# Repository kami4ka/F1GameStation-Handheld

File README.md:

<p align="right"><b>English</b> · <a href="README.uk.md">Українська</a></p>

<h1 align="center">F1GameStation</h1>

<p align="center">
  An open-source, PSP-style handheld for 8- and 16-bit games,<br>
  built around the Allwinner F1C200s and running a port of MiyooCFW.<br>
  <b>About $25 in parts, and every file is open.</b>
</p>

<p align="center">

</p>

<p align="center">
  <a href="https://kami4ka.github.io/F1GameStation-Handheld/"><b>Interactive 3D model and board viewer</b></a> ·
  <a href="docs/BUILD.md"><b>Build guide</b></a> ·
  <a href="https://kami4ka.github.io/F1GameStation-Handheld/ibom.html"><b>Interactive BOM</b></a> ·
  <a href="firmware/README.md"><b>Firmware</b></a>
</p>

> [!NOTE]
> **Rev 1 is a fully working console**: LCD, sound, buttons, battery, backlight and USB all work, and it
> plays games. It is still a first revision with [known issues](#known-issues), so expect some hand work
> while building one.

<p align="center">
  
</p>

## What it is

| | |
| --- | --- |
| **SoC** | Allwinner F1C200s (ARM926EJ-S, 64 MB DDR in package) |
| **Display** | 4.3" 480×272 RGB panel, 40-pin FPC (FPC043CS4001) |
| **Controls** | D-pad, A/B/X/Y, START, SELECT, MENU, PSP-style L/R triggers, side power button |
| **Power** | 1S Li-ion 606090 cell, IP5306 charger and boost, USB-C |
| **Audio** | SoC codec, NS4150B amplifier, on-board speaker |
| **Storage** | microSD (boot and games), optional 16 MB SPI flash |
| **Board** | 176 × 70 mm, 4 layers (JLC04161H-7628), JLCPCB assembly |
| **Case** | 186 × 80 mm, FDM-printed in PETG, M2 heat-set inserts |
| **Cost** | about $25 per unit (board share, parts, LCD, battery, filament) |
| **Firmware** | MiyooCFW 2.0 with a 480×272 kernel driver, a 480×272 gmenu2x and a cover-flow launcher |

## Repository

```
hardware/       KiCad 10 project, fab package (Gerbers, BOM with LCSC numbers,
                positions, schematic PDF, interactive BOM), PCBA STEP
enclosure/      print/   STL and 3MF files, two-colour labelled caps for Bambu printers
                source/  Fusion 360 archives (.f3d), STEP, parametric Fusion scripts
firmware/       miyoocfw/  kernel patches, device tree, SD card scripts, Docker build
                launcher/  the cover-flow game launcher
                emulator/  a QEMU model of the handheld for development without hardware
docs/           build guide, images
site/           the project site (3D viewer, KiCanvas), deployed to GitHub Pages
```

## Build one

The [build guide](docs/BUILD.md) walks through it step by step:

1. **Order the board** from JLCPCB with the files in [`hardware/production`](hardware/production).
2. **Finish the assembly**: the SoC and DC-DC are supplied by you, then the LCD, battery and speaker.
3. **Build the firmware** from source and flash it to a microSD card ([firmware/README.md](firmware/README.md)).
4. **Print the case** from [`enclosure/print`](enclosure/print).
5. **Close it up** with four M2 heat-set inserts, two filament pins and four M2 × 12 screws.

No hardware yet? The [emulator](firmware/emulator/README.md) boots the same SD card image on a Mac.

## Status

| Block | State |
| --- | --- |
| SoC, DRAM, FEL, U-Boot, SD boot | ✅ working on two boards |
| Power rails (EA3059C bucks, 3V0 LDO) | ✅ working |
| Buttons (13 inputs) | ✅ working, see PA1–PA3 below |
| MiyooCFW kernel, menu, emulators | ✅ boots and runs |
| LCD | ✅ working |
| Audio (codec, amplifier, speaker) | ✅ working |
| Battery gauge | ✅ working |
| Backlight | ✅ working |
| USB high speed | ✅ working |

### Known issues

- **L, R and MENU (PA1, PA2, PA3) have no pull-ups.** These pins belong to the SoC's touch-panel block,
  and their internal pull-ups have no effect. The firmware works around it by charging each line and
  reading it straight away. Rev 2 should add 10 kΩ external pull-ups to 3V3.
- **No pin-1 marks on the silkscreen.** Check the orientation of every IC, LED and polarised part
  against the [interactive BOM](hardware/production/F1GameStation-ibom.html) before soldering.
- The L/R trigger switches have no locating holes for their pegs; trim the pegs and fit them by hand.

## Gallery

Launcher screenshots are emulator captures with homebrew games and placeholder art.

## Credits

- [MiyooCFW](https://github.com/MiyooCFW) for the kernel, root filesystem, gmenu2x and the emulator builds this firmware is based on.
- The F1C200s core (SoC, DRAM, power, SD) comes from [FPVault](https://github.com/kami4ka/FPVault), the author's open-source onboard DVR for analog FPV, where it was tested over three board revisions.
- [KiCanvas](https://kicanvas.org), [InteractiveHtmlBom](https://github.com/openscopeproject/InteractiveHtmlBom) and [three.js](https://threejs.org) for the project site.

## License

- Hardware (`hardware/`, `enclosure/`): [CERN-OHL-S-2.0](hardware/LICENSE)
- Firmware (`firmware/`, `site/tools/`): [GPL-2.0](firmware/LICENSE). Third-party parts keep their own licences (DejaVu fonts, MiyooCFW, QEMU).
- Documentation and images (`docs/`): [CC BY-SA 4.0](docs/LICENSE)

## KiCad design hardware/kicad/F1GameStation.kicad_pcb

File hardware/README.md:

# Hardware

KiCad 10 project for the F1GameStation main board, Rev 1.

| Path | What |
| --- | --- |
| `kicad/F1GameStation.kicad_pro` | project; open this in KiCad |
| `kicad/*.kicad_sch` | schematic: top sheet plus `soc`, `power`, `storage`, `display`, `audio`, `buttons` |
| `kicad/F1GameStation.kicad_pcb` | 4-layer board, 176 × 70 mm |
| `kicad/libraries/` | project symbols, footprints and 3D models (most come from the LCSC/EasyEDA library) |
| `production/F1GameStation.zip` | Gerbers and drill files for JLCPCB |
| `production/bom.csv` | BOM grouped by part, with LCSC numbers |
| `production/positions.csv` | pick-and-place (both sides) |
| `production/netlist.ipc` | IPC-D-356 netlist for the electrical test |
| `production/F1GameStation-schematic.pdf` | schematic as PDF |
| `production/F1GameStation-ibom.html` | interactive BOM, open in a browser |
| `3d/F1GameStation_PCBA.step` | assembled board for mechanical CAD |

The board can also be browsed without KiCad on the
[project site](https://kami4ka.github.io/F1GameStation-Handheld/#hardware).

## Design notes

- **Stackup:** L1 signal, L2 GND, L3 power planes (3V3, 2V5, 1V2), L4 signal. Ground is
  carried by the L2 plane, outer pours and stitching vias, not by traces.
- **Sides:** buttons, LEDs and the speaker are on the front; every other part is on the back.
  Parts under the battery stay below 2.4 mm.
- **USB:** the D+/D− pair is coupled 0.16/0.1 mm with a 0.2 mm pour gap, about 90 Ω on JLC04161H-7628.
- **No vias in SMD pads**, except the thermal vias under exposed pads.
- **Power:** IP5306 charges the 1S cell from USB-C and boosts it to 5 V. An EA3059C makes 3V3, 2V5 and
  1V2; an XC6206 makes 3V0. The backlight driver is an MP3202 (PT4103 footprint and pinout).
- **Battery gauge:** +BATT through a 200k/100k divider to LRADC0 (KEYADC, SoC pin 79).
- **LCD:** 40-pin RGB565 panel on J2 (AFC24-S40FIA-00, contacts on both sides). Its pin numbering is
  reversed in the footprint because the panel's pin 1 lands on connector contact 40.
- **Debug:** UART0 on the TX/RX/GND pads on the back (2.54 mm row), FEL button SW2, Reset SW1.

## Rev 1 issues

- PA1–PA3 (MENU, L, R) need external pull-ups; firmware works around it for now.
- No pin-1 markers on the silkscreen.
- No locating holes for the L/R trigger switch pegs.

## License

[CERN-OHL-S-2.0](LICENSE).

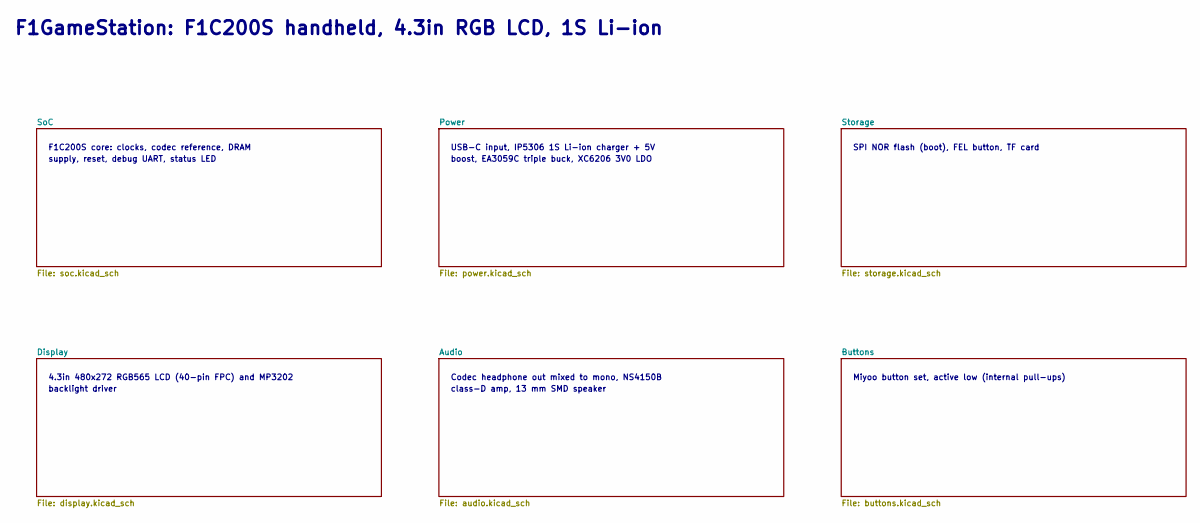
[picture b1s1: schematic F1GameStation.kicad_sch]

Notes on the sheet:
F1GameStation: F1C200S handheld, 4.3in RGB LCD, 1S Li-ion
F1C200S core: clocks, codec reference, DRAM
supply, reset, debug UART, status LED
USB-C input, IP5306 1S Li-ion charger + 5V
boost, EA3059C triple buck, XC6206 3V0 LDO
SPI NOR flash (boot), FEL button, TF card
4.3in 480x272 RGB565 LCD (40-pin FPC) and MP3202
backlight driver
Codec headphone out mixed to mono, NS4150B
class-D amp, 13 mm SMD speaker
Miyoo button set, active low (internal pull-ups)

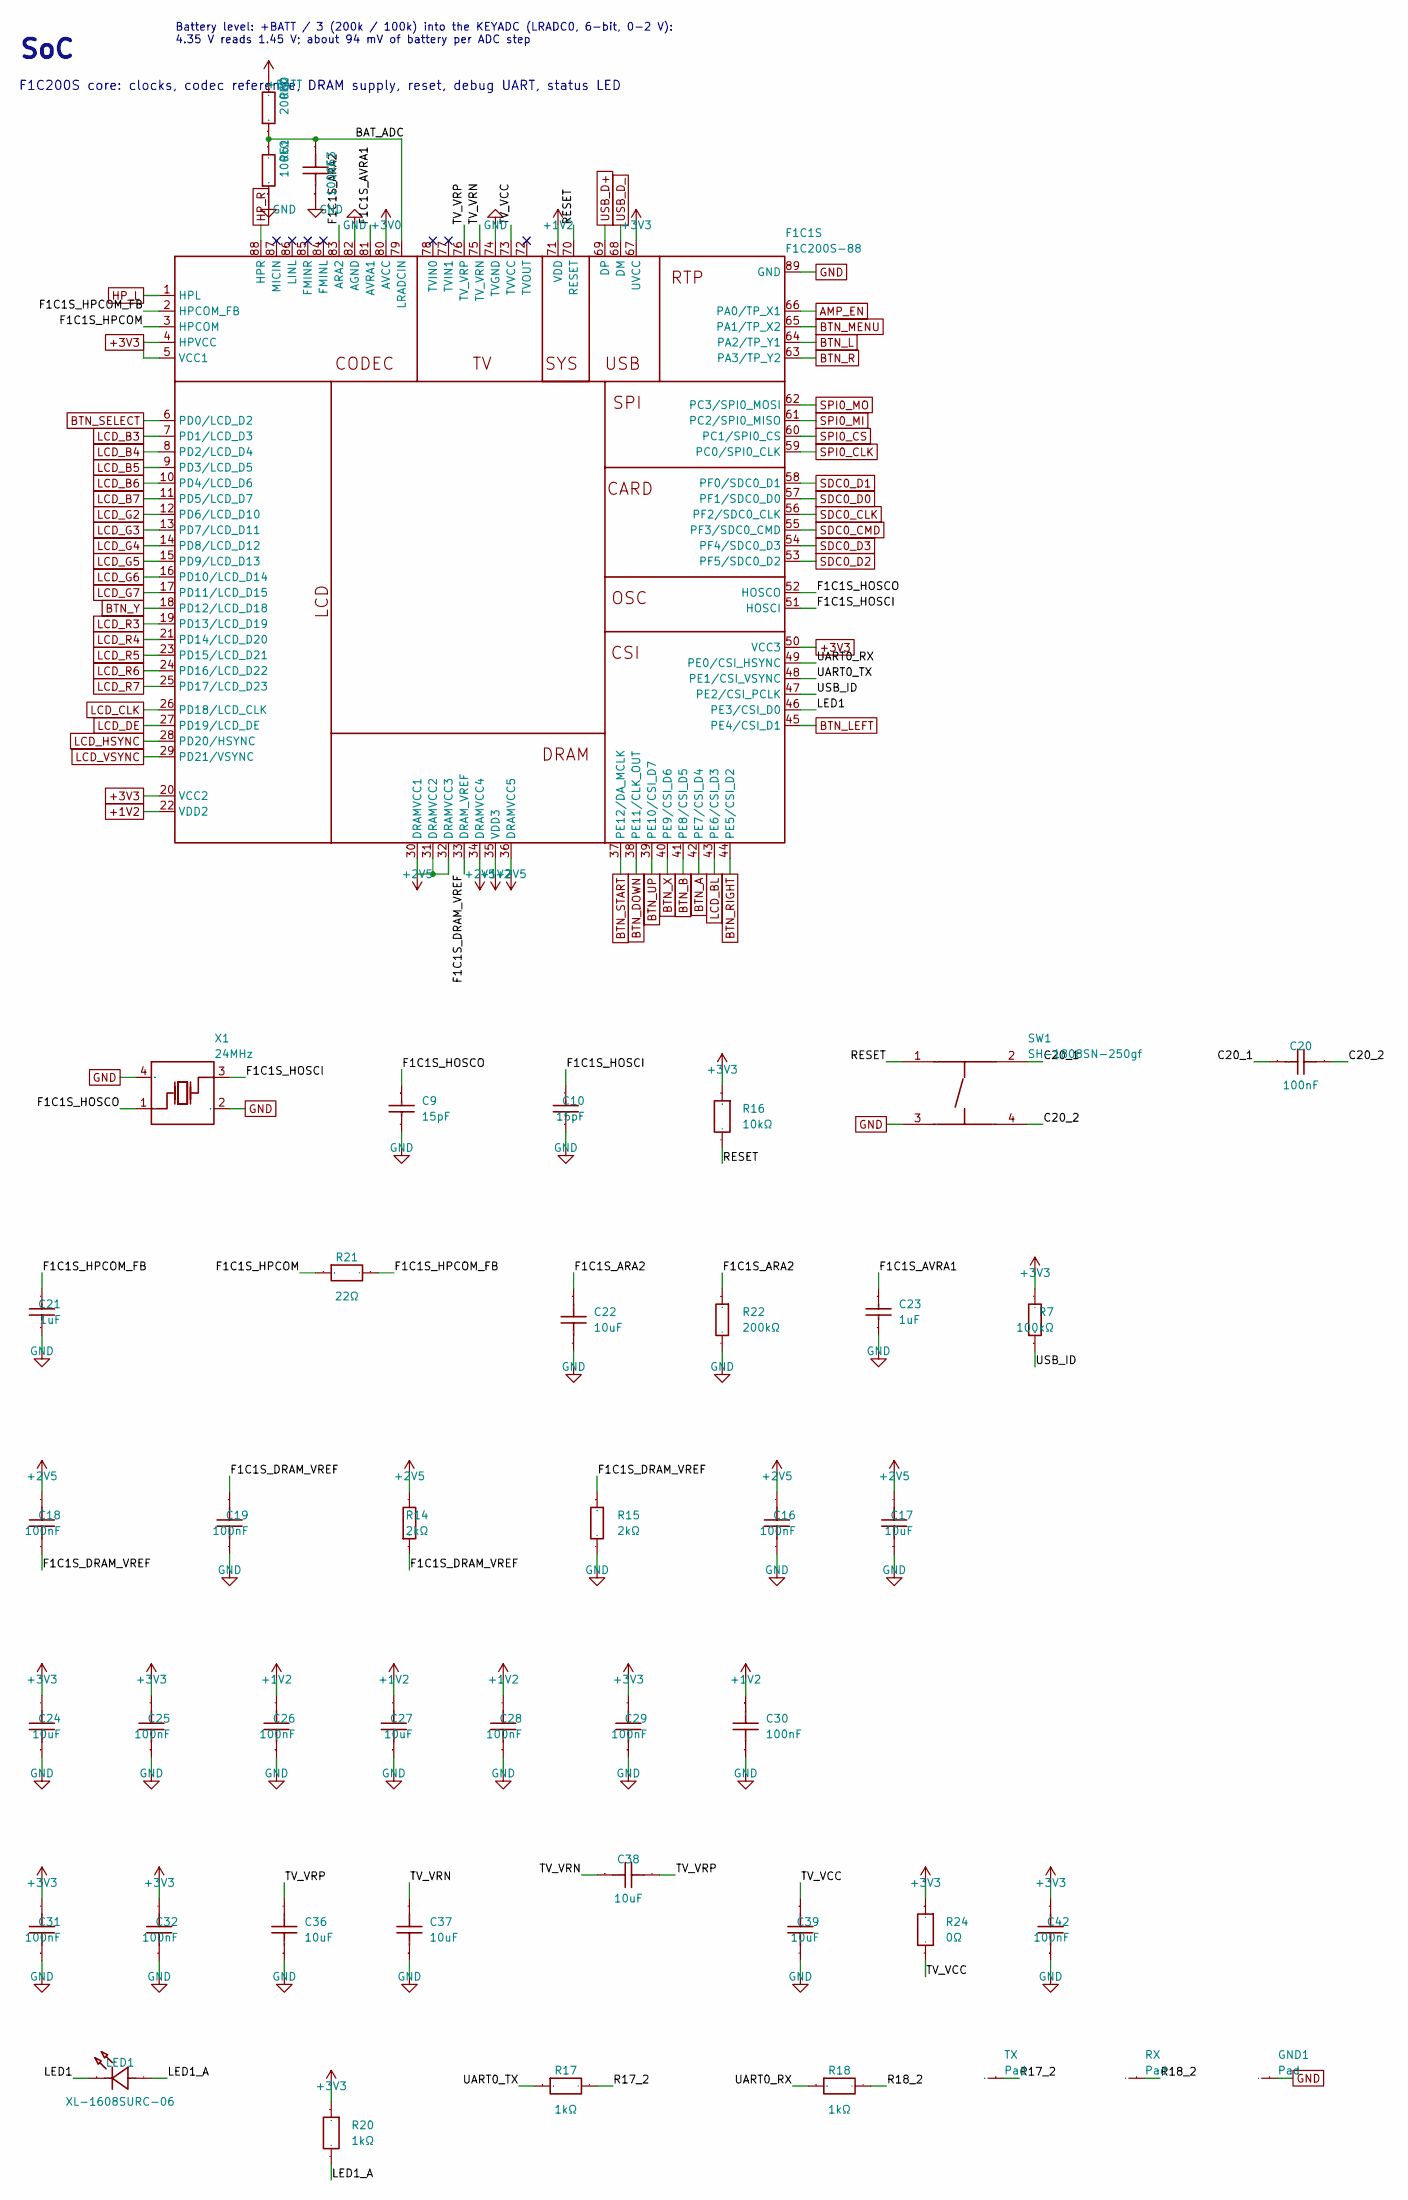
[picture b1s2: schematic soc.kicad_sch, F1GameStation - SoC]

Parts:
C9, C10: 15pF; C0603; Tolerance ±5%; Voltage Rating 50V; Manufacturer Part CL10C150JB8NNNC; LCSC C1644
C16, C18, C19, C20, C25, C26, C28, C29, C30, C31, C32, C63: 100nF; C0603; Tolerance ±10%; Voltage Rating 50V; Manufacturer Part CL10B104KB8NNNC; LCSC C1591
C17, C22, C24, C27: 10uF; C0603; Tolerance ±20%; Voltage Rating 25V; Manufacturer Part TCC0603X5R106M160CT; LCSC C380317
C21, C23: 1uF; C0603; Tolerance ±10%; Voltage Rating 25V; Manufacturer Part CL10B105KA8NNNC; LCSC C29936
C36, C37, C38, C39: 10uF; C0603; Tolerance ±20%; Voltage Rating 16V; Manufacturer Part TCC0603X5R106M160CT; LCSC C380317
C42: 100nF; C0603; Tolerance ±10%; Voltage Rated 50V; Manufacturer Part CC0603KRX7R9BB104; LCSC C14663
F1C1S: F1C200S-88; QFN-88_L10.0-W10.0-P0.40-BL-EP; Manufacturer Part F1C200S; LCSC C2879851
GND1: Pad; PAD
LED1: XL-1608SURC-06; LED0603-RD_RED; Voltage - Forward(Vf) 2.3V; Manufacturer Part XL-1608SURC-06; LCSC C965799
R7, R51: 100kΩ; R0603; Tolerance ±1%; Voltage-Supply(Max) 75V; Manufacturer Part RC0603FR-07100KL; LCSC C14675
R14, R15: 2kΩ; R0603; Tolerance ±1%; Voltage-Supply(Max) 75V; Manufacturer Part RC0603FR-072KL; LCSC C105576
R16: 10kΩ; R0603; Tolerance ±1%; Manufacturer Part CRCW060310K0FKEA; LCSC C844918
R17, R18, R20: 1kΩ; R0603; Tolerance ±1%; Voltage-Supply(Max) 75V; Manufacturer Part FRC0603F1001TS; LCSC C2907002
R21: 22Ω; R0603; Tolerance ±1%; Voltage-Supply(Max) 75V; Manufacturer Part FRC0603F22R0TS; LCSC C2930077
R22, R50: 200kΩ; R0603; Tolerance ±1%; Manufacturer Part RC0603FR-07200KL; LCSC C105574
R24: 0Ω; R0603; Tolerance ±5%; Voltage-Supply(Max) 75V; Manufacturer Part 1RC0603J0000; LCSC C54531634
RX: Pad; PAD
SW1: SH-1808SN-250gf; SW-SMD_4P-L4.2-W3.4-P2.15-LS5.2; Voltage Rating 12V; Manufacturer Part SH-1808SN-250gf; LCSC C52092028
TX: Pad; PAD
X1: 24MHz; CRYSTAL-SMD_4P-L3.2-W2.5-BL; Manufacturer Part X322524MOB4SI; LCSC C70590

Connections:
+1V2: C26.2, C27.2, C28.2, C30.1, F1C1S.22 (VDD2), F1C1S.35 (VDD3), F1C1S.71 (VDD); also elsewhere on the board
+2V5: C16.2, C17.2, C18.2, F1C1S.30 (DRAMVCC1), F1C1S.31 (DRAMVCC2), F1C1S.32 (DRAMVCC3), F1C1S.34 (DRAMVCC4), F1C1S.36 (DRAMVCC5), R14.2; also elsewhere on the board
+3V0: F1C1S.80 (AVCC); also elsewhere on the board
+3V3: C24.2, C25.2, C29.2, C31.2, C32.2, C42.2, F1C1S.4 (HPVCC), F1C1S.5 (VCC1), F1C1S.20 (VCC2), F1C1S.50 (VCC3), F1C1S.67 (UVCC), R7.2, R16.1, R20.1, R24.1; also elsewhere on the board
+BATT: R50.2; also elsewhere on the board
/SoC/BAT_ADC: C63.2, F1C1S.79 (LRADCIN), R50.1, R51.2
/SoC/C20_1: C20.1, SW1.2
/SoC/C20_2: C20.2, SW1.4
/SoC/F1C1S_ARA2: C22.1, F1C1S.83 (ARA2), R22.1
/SoC/F1C1S_AVRA1: C23.1, F1C1S.81 (AVRA1)
/SoC/F1C1S_DRAM_VREF: C18.1, C19.2, F1C1S.33 (DRAM_VREF), R14.1, R15.1
/SoC/F1C1S_HOSCI: C10.2, F1C1S.51 (HOSCI), X1.3 (OSC2)
/SoC/F1C1S_HOSCO: C9.1, F1C1S.52 (HOSCO), X1.1 (OSC1)
/SoC/F1C1S_HPCOM: F1C1S.3 (HPCOM), R21.1
/SoC/F1C1S_HPCOM_FB: C21.2, F1C1S.2 (HPCOM_FB), R21.2
/SoC/LED1: F1C1S.46 (PE3/CSI_D0), LED1.1 (K)
/SoC/LED1_A: LED1.2 (A), R20.2
/SoC/R17_2: R17.2, TX.1
/SoC/R18_2: R18.2, RX.1
/SoC/RESET: F1C1S.70 (RESET), R16.2, SW1.1
/SoC/TV_VCC: C39.1, F1C1S.73 (TVVCC), R24.2
/SoC/TV_VRN: C37.2, C38.1, F1C1S.75 (TV_VRN)
/SoC/TV_VRP: C36.2, C38.2, F1C1S.76 (TV_VRP)
/SoC/UART0_RX: F1C1S.49 (PE0/CSI_HSYNC), R18.1
/SoC/UART0_TX: F1C1S.48 (PE1/CSI_VSYNC), R17.1
/SoC/USB_ID: F1C1S.47 (PE2/CSI_PCLK), R7.1
AMP_EN: F1C1S.66 (PA0/TP_X1); also elsewhere on the board
BTN_A: F1C1S.42 (PE7/CSI_D4); also elsewhere on the board
BTN_B: F1C1S.41 (PE8/CSI_D5); also elsewhere on the board
BTN_DOWN: F1C1S.38 (PE11/CLK_OUT); also elsewhere on the board
BTN_L: F1C1S.64 (PA2/TP_Y1); also elsewhere on the board
BTN_LEFT: F1C1S.45 (PE4/CSI_D1); also elsewhere on the board
BTN_MENU: F1C1S.65 (PA1/TP_X2); also elsewhere on the board
BTN_R: F1C1S.63 (PA3/TP_Y2); also elsewhere on the board
BTN_RIGHT: F1C1S.44 (PE5/CSI_D2); also elsewhere on the board
BTN_SELECT: F1C1S.6 (PD0/LCD_D2); also elsewhere on the board
BTN_START: F1C1S.37 (PE12/DA_MCLK); also elsewhere on the board
BTN_UP: F1C1S.39 (PE10/CSI_D7); also elsewhere on the board
BTN_X: F1C1S.40 (PE9/CSI_D6); also elsewhere on the board
BTN_Y: F1C1S.18 (PD12/LCD_D18); also elsewhere on the board
GND: C9.2, C10.1, C16.1, C17.1, C19.1, C21.1, C22.2, C23.2, C24.1, C25.1, C26.1, C27.1, C28.1, C29.1, C30.2, C31.1, C32.1, C36.1, C37.1, C39.2, C42.1, C63.1, F1C1S.74 (TVGND), F1C1S.82 (AGND), F1C1S.89 (GND), GND1.1, R15.2, R22.2, R51.1, SW1.3, X1.2 (GND), X1.4 (GND); also elsewhere on the board
HP_L: F1C1S.1 (HPL); also elsewhere on the board
HP_R: F1C1S.88 (HPR); also elsewhere on the board
LCD_B3: F1C1S.7 (PD1/LCD_D3); also elsewhere on the board
LCD_B4: F1C1S.8 (PD2/LCD_D4); also elsewhere on the board
LCD_B5: F1C1S.9 (PD3/LCD_D5); also elsewhere on the board
LCD_B6: F1C1S.10 (PD4/LCD_D6); also elsewhere on the board
LCD_B7: F1C1S.11 (PD5/LCD_D7); also elsewhere on the board
LCD_BL: F1C1S.43 (PE6/CSI_D3); also elsewhere on the board
LCD_CLK: F1C1S.26 (PD18/LCD_CLK); also elsewhere on the board
LCD_DE: F1C1S.27 (PD19/LCD_DE); also elsewhere on the board
LCD_G2: F1C1S.12 (PD6/LCD_D10); also elsewhere on the board
LCD_G3: F1C1S.13 (PD7/LCD_D11); also elsewhere on the board
LCD_G4: F1C1S.14 (PD8/LCD_D12); also elsewhere on the board
LCD_G5: F1C1S.15 (PD9/LCD_D13); also elsewhere on the board
LCD_G6: F1C1S.16 (PD10/LCD_D14); also elsewhere on the board
LCD_G7: F1C1S.17 (PD11/LCD_D15); also elsewhere on the board
LCD_HSYNC: F1C1S.28 (PD20/HSYNC); also elsewhere on the board
LCD_R3: F1C1S.19 (PD13/LCD_D19); also elsewhere on the board
LCD_R4: F1C1S.21 (PD14/LCD_D20); also elsewhere on the board
LCD_R5: F1C1S.23 (PD15/LCD_D21); also elsewhere on the board
LCD_R6: F1C1S.24 (PD16/LCD_D22); also elsewhere on the board
LCD_R7: F1C1S.25 (PD17/LCD_D23); also elsewhere on the board
LCD_VSYNC: F1C1S.29 (PD21/VSYNC); also elsewhere on the board
SDC0_CLK: F1C1S.56 (PF2/SDC0_CLK); also elsewhere on the board
SDC0_CMD: F1C1S.55 (PF3/SDC0_CMD); also elsewhere on the board
SDC0_D0: F1C1S.57 (PF1/SDC0_D0); also elsewhere on the board
SDC0_D1: F1C1S.58 (PF0/SDC0_D1); also elsewhere on the board
SDC0_D2: F1C1S.53 (PF5/SDC0_D2); also elsewhere on the board
SDC0_D3: F1C1S.54 (PF4/SDC0_D3); also elsewhere on the board
SPI0_CLK: F1C1S.59 (PC0/SPI0_CLK); also elsewhere on the board
SPI0_CS: F1C1S.60 (PC1/SPI0_CS); also elsewhere on the board
SPI0_MI: F1C1S.61 (PC2/SPI0_MISO); also elsewhere on the board
SPI0_MO: F1C1S.62 (PC3/SPI0_MOSI); also elsewhere on the board
USB_D+: F1C1S.69 (DP); also elsewhere on the board
USB_D_: F1C1S.68 (DM); also elsewhere on the board

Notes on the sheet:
SoC
F1C200S core: clocks, codec reference, DRAM supply, reset, debug UART, status LED
Battery level: +BATT / 3 (200k / 100k) into the KEYADC (LRADC0, 6-bit, 0-2 V): 4.35 V reads 1.45 V; about 94 mV of battery per ADC step

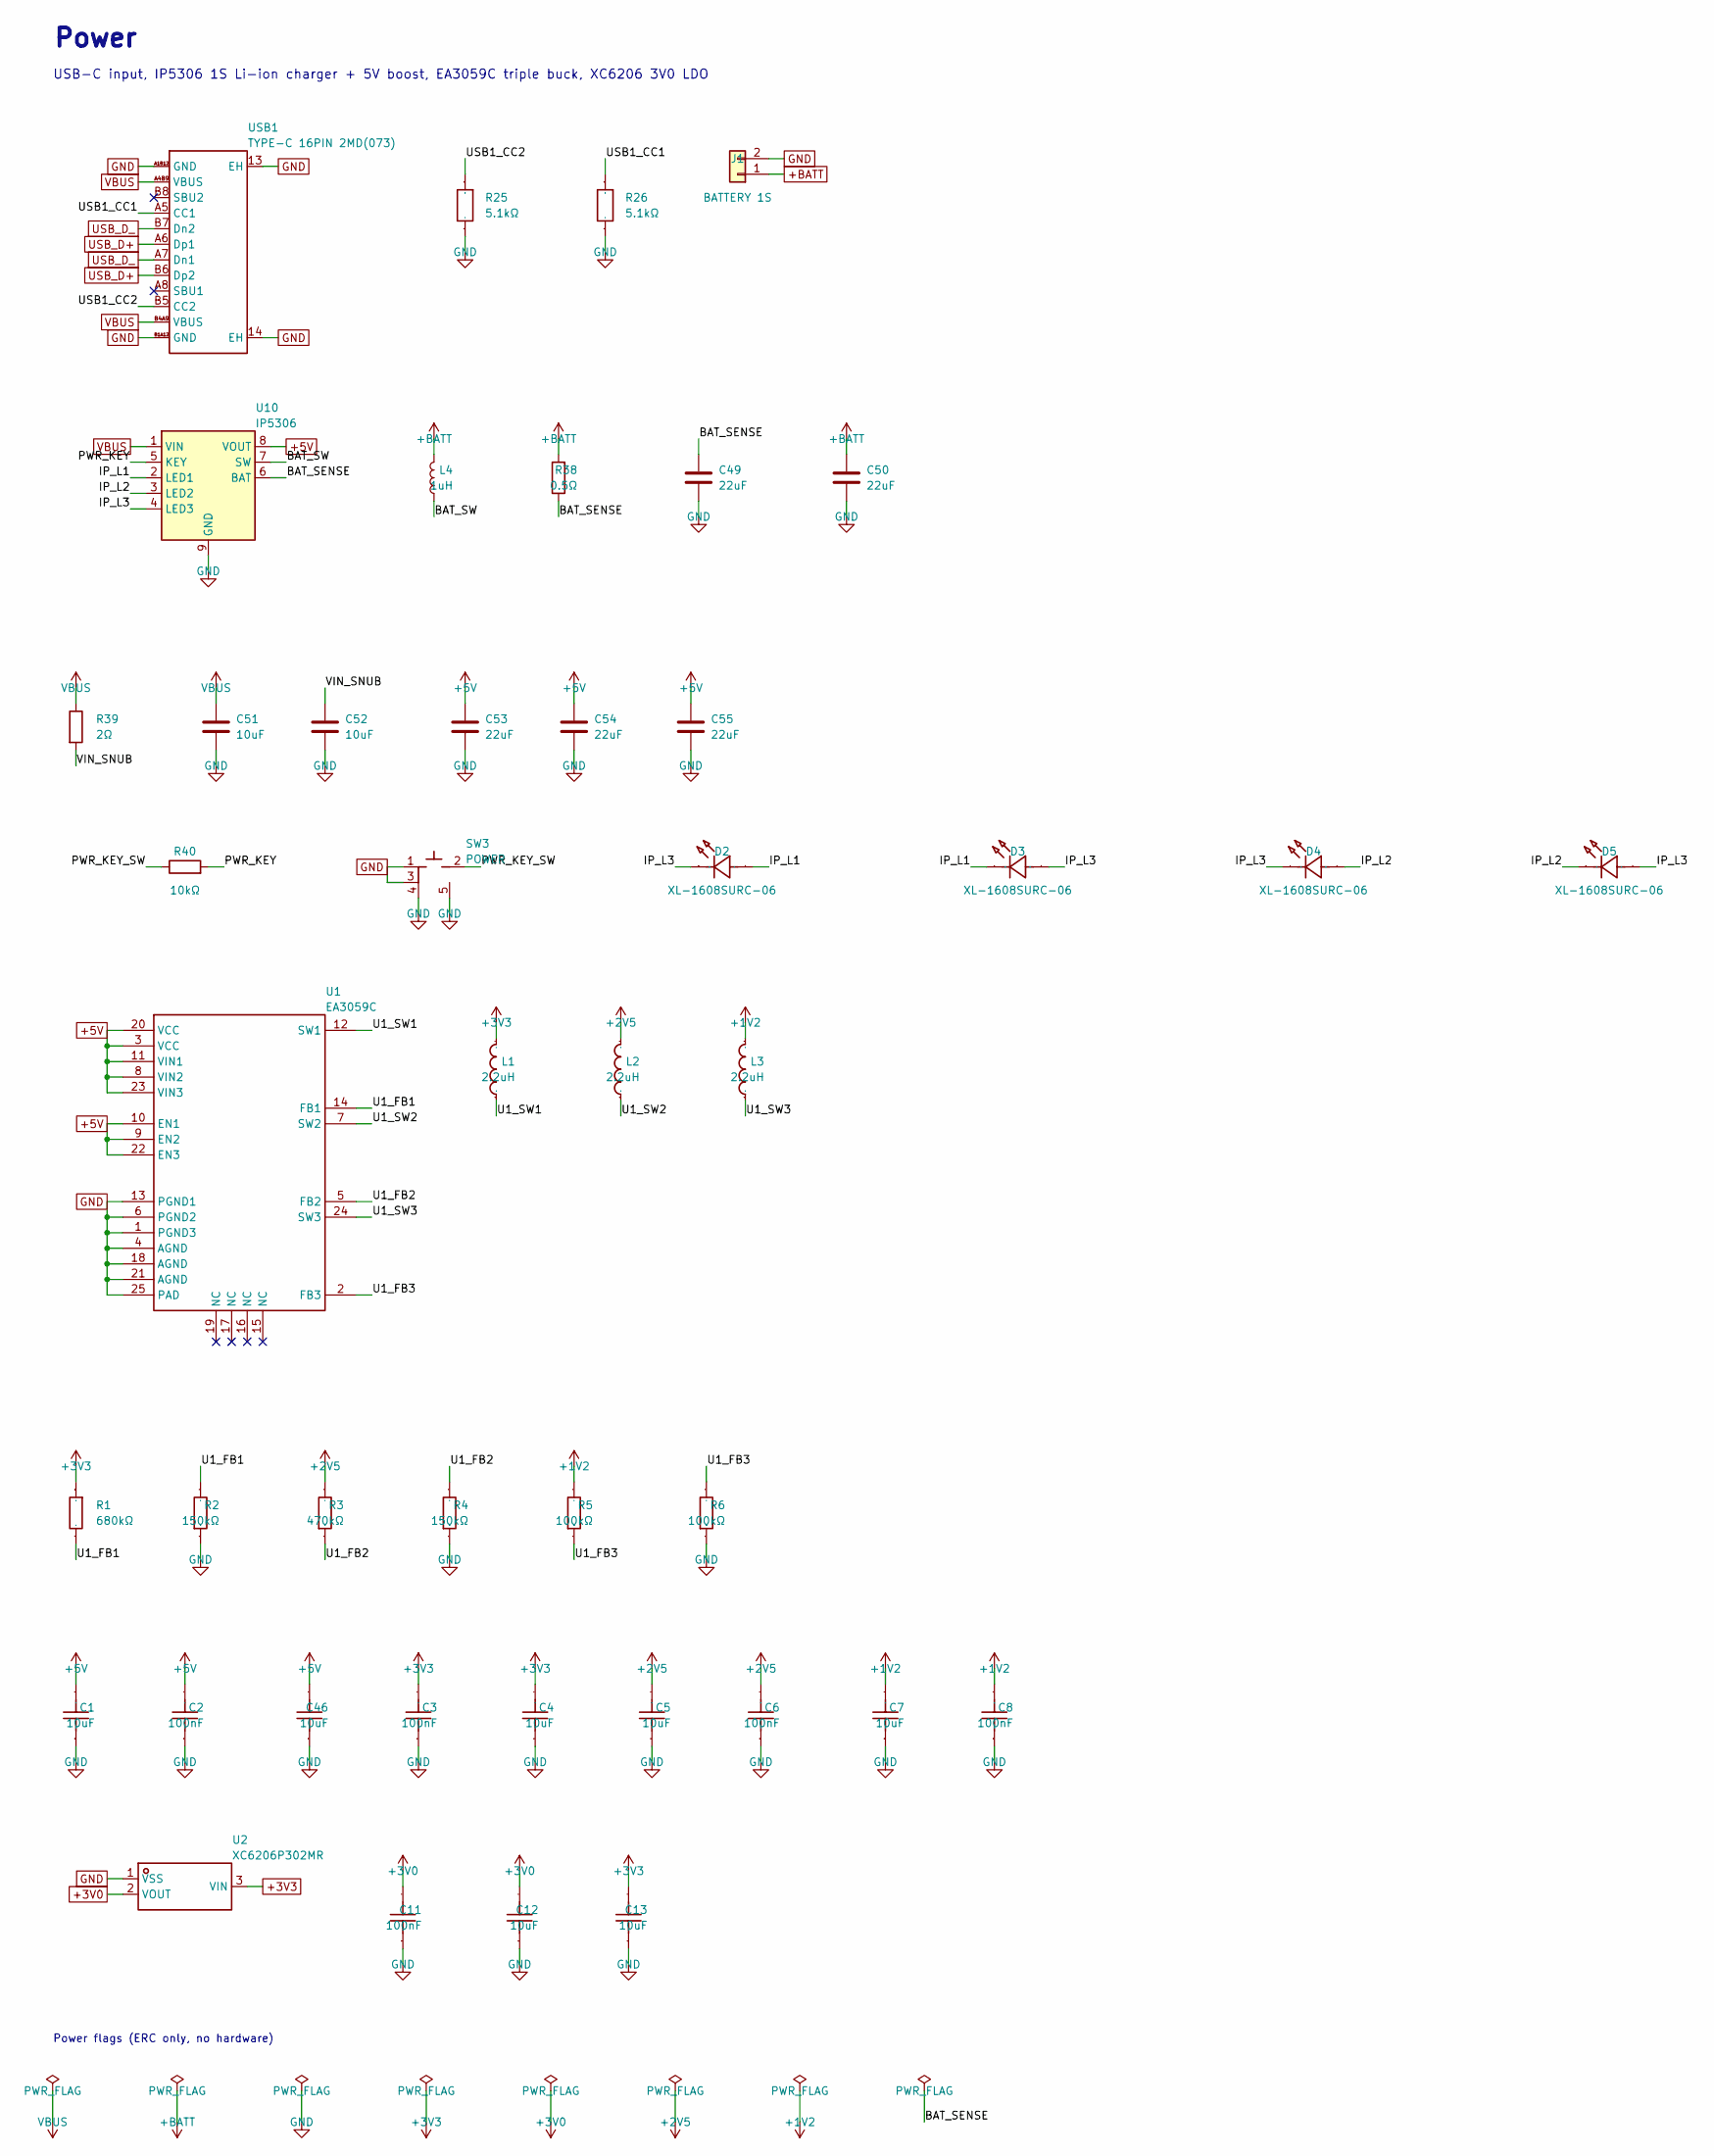
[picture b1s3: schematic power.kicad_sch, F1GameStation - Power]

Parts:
C1, C4, C5, C7, C12, C13, C46: 10uF; C0603; Tolerance ±20%; Voltage Rating 25V; Manufacturer Part TCC0603X5R106M160CT; LCSC C380317
C2, C3, C6, C8, C11: 100nF; C0603; Tolerance ±10%; Voltage Rating 50V; Manufacturer Part CL10B104KB8NNNC; LCSC C1591
C49, C50, C53, C54, C55: 22uF; C_0805_2012Metric; Manufacturer Part CL21A226MAQNNNE; LCSC C45783
C51, C52: 10uF; C_0805_2012Metric; Manufacturer Part CL21A106KAYNNNE; LCSC C15850
D2, D3, D4, D5: XL-1608SURC-06; LED0603-RD_RED; Manufacturer Part XL-1608SURC-06; LCSC C965799
J1: BATTERY 1S; JST_PH_S2B-PH-SM4-TB_1x02-1MP_P2.00mm_Horizontal; Manufacturer Part S2B-PH-SM4-TB(LF)(SN); LCSC C295747
L1, L2, L3: 2.2uH; IND-SMD_L2.5-W2.0-B; Current Rating 2.5A; Tolerance ±20%; Manufacturer Part SPM2510-2R2MA; LCSC C7471148
L4: 1uH; L_Changjiang_FXL0630; Manufacturer Part FXL0630-1R0-M; LCSC C167216
R1: 680kΩ; R0603; Tolerance ±1%; Manufacturer Part RC0603FR-07680KL; LCSC C137690
R2, R4: 150kΩ; R0603; Tolerance ±1%; Manufacturer Part RC0603FR-07150KL; LCSC C114660
R3: 470kΩ; R0603; Tolerance ±1%; Voltage-Supply(Max) 75V; Manufacturer Part RC0603FR-07470KL; LCSC C114622
R5, R6: 100kΩ; R0603; Tolerance ±1%; Voltage-Supply(Max) 75V; Manufacturer Part RC0603FR-07100KL; LCSC C14675
R25, R26: 5.1kΩ; R0603; Tolerance ±1%; Voltage-Supply(Max) 75V; Manufacturer Part FRC0603F5101TS; LCSC C2907044
R38: 0.5Ω; R_0603_1608Metric; Manufacturer Part 0603WAF500LT5E; LCSC C45312
R39: 2Ω; R_0603_1608Metric; Manufacturer Part 0603WAF200KT5E; LCSC C22977
R40: 10kΩ; R_0603_1608Metric; Manufacturer Part 0603WAF1002T5E; LCSC C25804
SW3: POWER; SKRTLAE010; Manufacturer Part SKRTLAE010; LCSC C110293
U1: EA3059C; QFN-24_L4.0-W4.0-P0.50-BL-EP2.6; Manufacturer Part EA3059CQDR; LCSC C570858
U2: XC6206P302MR; SOT-23-3_L3.0-W1.7-P0.95-LS2.9-BR; Output Voltage 3V; Voltage - Supply 8V; Manufacturer Part XC6206P302MR; LCSC C347375
U10: IP5306; SOIC-8-1EP_3.9x4.9mm_P1.27mm_EP2.29x3mm_ThermalVias; Manufacturer Part IP5306; LCSC C181692
USB1: TYPE-C 16PIN 2MD(073); USB-C-SMD_TYPE-C-16PIN-2MD-073; Current Rating-Power 3A; Voltage Rating 5V; Manufacturer Part TYPE-C 16PIN 2MD(073); LCSC C2765186

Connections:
+1V2: C7.2, C8.2, L3.2, R5.2; also elsewhere on the board
+2V5: C5.2, C6.2, L2.2, R3.2; also elsewhere on the board
+3V0: C11.2, C12.2, U2.2 (VOUT); also elsewhere on the board
+3V3: C3.2, C4.2, C13.2, L1.2, R1.1, U2.3 (VIN); also elsewhere on the board
+5V: C1.2, C2.2, C46.2, C53.1, C54.1, C55.1, U1.3 (VCC), U1.8 (VIN2), U1.9 (EN2), U1.10 (EN1), U1.11 (VIN1), U1.20 (VCC), U1.22 (EN3), U1.23 (VIN3), U10.8 (VOUT); also elsewhere on the board
+BATT: C50.1, J1.1, L4.2, R38.2; also elsewhere on the board
/Power/BAT_SENSE: C49.1, R38.1, U10.6 (BAT)
/Power/BAT_SW: L4.1, U10.7 (SW)
/Power/IP_L1: D2.2 (A), D3.1 (K), U10.2 (LED1)
/Power/IP_L2: D4.2 (A), D5.1 (K), U10.3 (LED2)
/Power/IP_L3: D2.1 (K), D3.2 (A), D4.1 (K), D5.2 (A), U10.4 (LED3)
/Power/PWR_KEY: R40.2, U10.5 (KEY)
/Power/PWR_KEY_SW: R40.1, SW3.2
/Power/U1_FB1: R1.2, R2.2, U1.14 (FB1)
/Power/U1_FB2: R3.1, R4.2, U1.5 (FB2)
/Power/U1_FB3: R5.1, R6.2, U1.2 (FB3)
/Power/U1_SW1: L1.1, U1.12 (SW1)
/Power/U1_SW2: L2.1, U1.7 (SW2)
/Power/U1_SW3: L3.1, U1.24 (SW3)
/Power/USB1_CC1: R26.1, USB1.A5 (CC1)
/Power/USB1_CC2: R25.1, USB1.B5 (CC2)
/Power/VIN_SNUB: C52.1, R39.2
GND: C1.1, C2.1, C3.1, C4.1, C5.1, C6.1, C7.1, C8.1, C11.1, C12.1, C13.1, C46.1, C49.2, C50.2, C51.2, C52.2, C53.2, C54.2, C55.2, J1.2, R2.1, R4.1, R6.1, R25.2, R26.2, SW3.1, SW3.3, SW3.4, SW3.5, U1.1 (PGND3), U1.4 (AGND), U1.6 (PGND2), U1.13 (PGND1), U1.18 (AGND), U1.21 (AGND), U1.25 (PAD), U2.1 (VSS), U10.9 (GND), USB1.13 (EH), USB1.14 (EH), USB1.A1B12 (GND), USB1.B1A12 (GND); also elsewhere on the board
USB_D+: USB1.A6 (Dp1), USB1.B6 (Dp2); also elsewhere on the board
USB_D_: USB1.A7 (Dn1), USB1.B7 (Dn2); also elsewhere on the board
VBUS: C51.1, R39.1, U10.1 (VIN), USB1.A4B9 (VBUS), USB1.B4A9 (VBUS)

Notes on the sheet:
Power
USB-C input, IP5306 1S Li-ion charger + 5V boost, EA3059C triple buck, XC6206 3V0 LDO
Power flags (ERC only, no hardware)

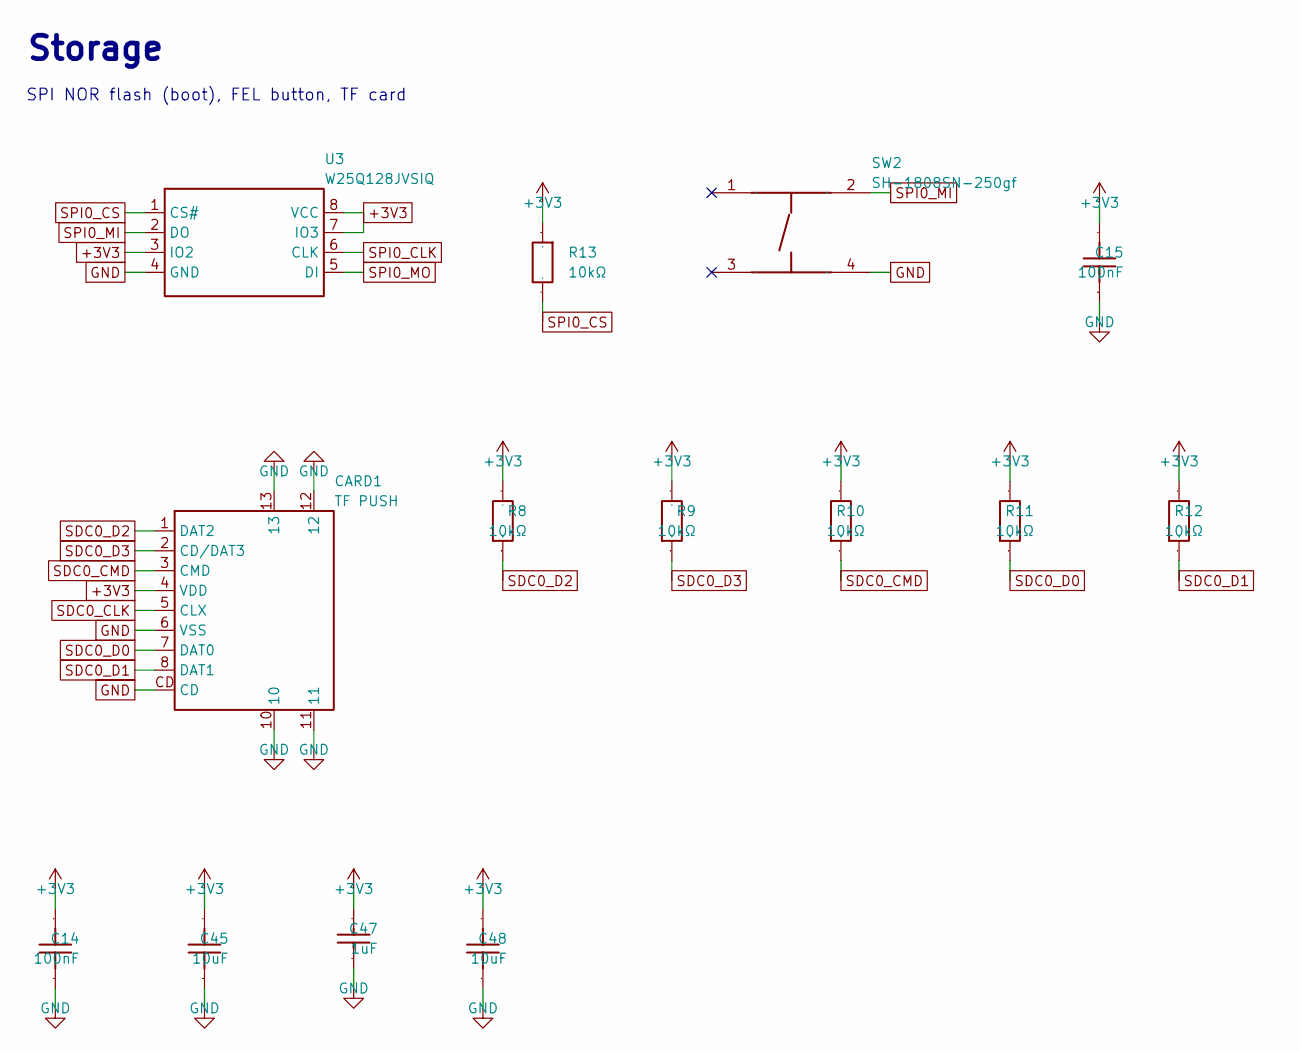
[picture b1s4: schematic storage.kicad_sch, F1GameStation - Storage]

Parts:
C14, C15: 100nF; C0603; Tolerance ±10%; Voltage Rating 50V; Manufacturer Part CL10B104KB8NNNC; LCSC C1591
C45: 10uF; C0603; Manufacturer Part CL10A106KP8NNNC; LCSC C19702
C47: 1uF; C0603; Tolerance ±10%; Voltage Rating 25V; Manufacturer Part CL10B105KA8NNNC; LCSC C29936
C48: 10uF; C0603; Tolerance ±20%; Voltage Rating 25V; Manufacturer Part TCC0603X5R106M160CT; LCSC C380317
CARD1: TF PUSH; TF-SMD_TF-PUSH; Manufacturer Part TF PUSH; LCSC C393941
R8, R9, R10, R11, R12, R13: 10kΩ; R0603; Tolerance ±1%; Manufacturer Part CRCW060310K0FKEA; LCSC C844918
SW2: SH-1808SN-250gf; SW-SMD_4P-L4.2-W3.4-P2.15-LS5.2; Voltage Rating 12V; Manufacturer Part SH-1808SN-250gf; LCSC C52092028
U3: W25Q128JVSIQ; SOIC-8_L5.3-W5.3-P1.27-LS8.0-BL; Voltage - Supply 2.7V~3.6V; Manufacturer Part W25Q128JVSIQ; LCSC C97521

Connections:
+3V3: C14.2, C15.2, C45.2, C47.2, C48.2, CARD1.4 (VDD), R8.2, R9.2, R10.2, R11.2, R12.2, R13.1, U3.3 (IO2), U3.7 (IO3), U3.8 (VCC); also elsewhere on the board
GND: C14.1, C15.1, C45.1, C47.1, C48.1, CARD1.6 (VSS), CARD1.10, CARD1.11, CARD1.12, CARD1.13, CARD1.CD, SW2.4, U3.4 (GND); also elsewhere on the board
SDC0_CLK: CARD1.5 (CLX); also elsewhere on the board
SDC0_CMD: CARD1.3 (CMD), R10.1; also elsewhere on the board
SDC0_D0: CARD1.7 (DAT0), R11.1; also elsewhere on the board
SDC0_D1: CARD1.8 (DAT1), R12.1; also elsewhere on the board
SDC0_D2: CARD1.1 (DAT2), R8.1; also elsewhere on the board
SDC0_D3: CARD1.2 (CD/DAT3), R9.1; also elsewhere on the board
SPI0_CLK: U3.6 (CLK); also elsewhere on the board
SPI0_CS: R13.2, U3.1 (CS#); also elsewhere on the board
SPI0_MI: SW2.2, U3.2 (DO); also elsewhere on the board
SPI0_MO: U3.5 (DI); also elsewhere on the board

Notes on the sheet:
Storage
SPI NOR flash (boot), FEL button, TF card

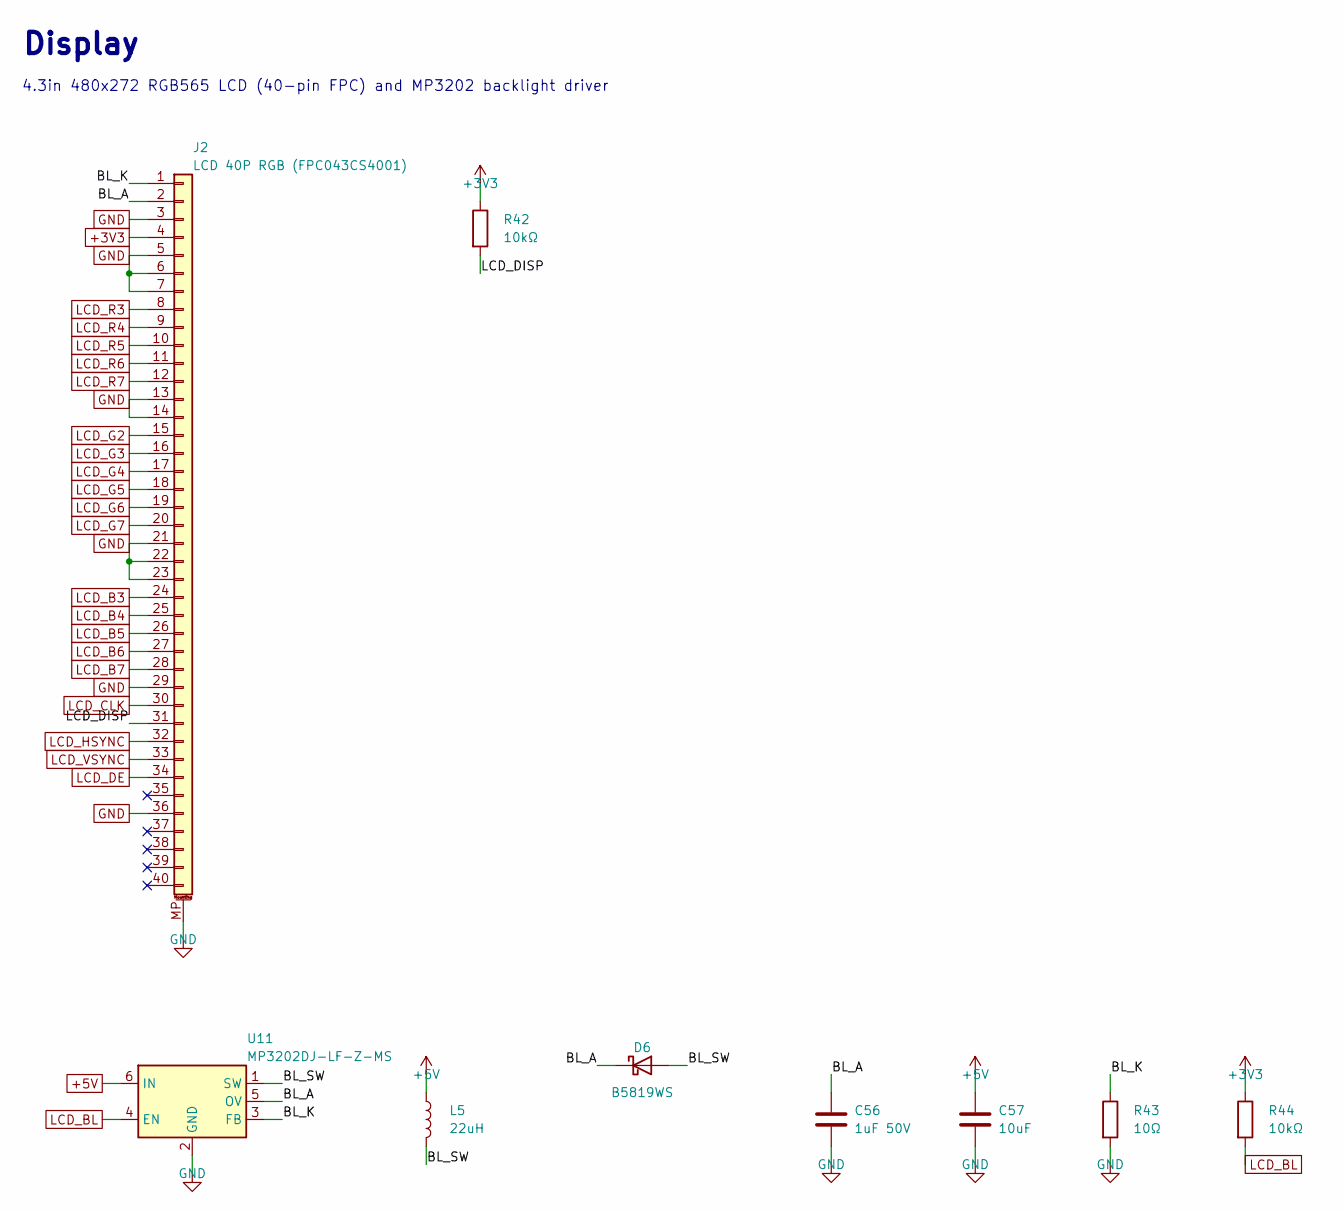
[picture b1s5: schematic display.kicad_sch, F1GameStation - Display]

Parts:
C56: 1uF 50V; C_0805_2012Metric; Manufacturer Part CC0805KKX7R9BB105; LCSC C91185
C57: 10uF; C_0805_2012Metric; Manufacturer Part CL21A106KAYNNNE; LCSC C15850
D6: B5819WS; D_SOD-323; Manufacturer Part B5819WS; LCSC C64886
J2: LCD 40P RGB (FPC043CS4001); AFC24-S40FIA-00_REV; Manufacturer Part AFC24-S40FIA-00; LCSC C262686
L5: 22uH; L_Sunlord_SWPA4020S; Manufacturer Part FNR4020S220MT; LCSC C167838
R42, R44: 10kΩ; R_0603_1608Metric; Manufacturer Part 0603WAF1002T5E; LCSC C25804
R43: 10Ω; R_0603_1608Metric; Manufacturer Part 0603WAF100JT5E; LCSC C22859
U11: MP3202DJ-LF-Z-MS; SOT-23-6; Manufacturer Part MP3202DJ-LF-Z-MS; LCSC C52988868

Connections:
+3V3: J2.4, R42.1, R44.1; also elsewhere on the board
+5V: C57.1, L5.1, U11.6 (IN); also elsewhere on the board
/Display/BL_A: C56.1, D6.1 (K), J2.2, U11.5 (OV)
/Display/BL_K: J2.1, R43.1, U11.3 (FB)
/Display/BL_SW: D6.2 (A), L5.2, U11.1 (SW)
/Display/LCD_DISP: J2.31, R42.2
GND: C56.2, C57.2, J2.3, J2.5, J2.6, J2.7, J2.13, J2.14, J2.21, J2.22, J2.23, J2.29, J2.36, J2.MP (MountPin), R43.2, U11.2 (GND); also elsewhere on the board
LCD_B3: J2.24; also elsewhere on the board
LCD_B4: J2.25; also elsewhere on the board
LCD_B5: J2.26; also elsewhere on the board
LCD_B6: J2.27; also elsewhere on the board
LCD_B7: J2.28; also elsewhere on the board
LCD_BL: R44.2, U11.4 (EN); also elsewhere on the board
LCD_CLK: J2.30; also elsewhere on the board
LCD_DE: J2.34; also elsewhere on the board
LCD_G2: J2.15; also elsewhere on the board
LCD_G3: J2.16; also elsewhere on the board
LCD_G4: J2.17; also elsewhere on the board
LCD_G5: J2.18; also elsewhere on the board
LCD_G6: J2.19; also elsewhere on the board
LCD_G7: J2.20; also elsewhere on the board
LCD_HSYNC: J2.32; also elsewhere on the board
LCD_R3: J2.8; also elsewhere on the board
LCD_R4: J2.9; also elsewhere on the board
LCD_R5: J2.10; also elsewhere on the board
LCD_R6: J2.11; also elsewhere on the board
LCD_R7: J2.12; also elsewhere on the board
LCD_VSYNC: J2.33; also elsewhere on the board

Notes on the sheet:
Display
4.3in 480x272 RGB565 LCD (40-pin FPC) and MP3202 backlight driver
